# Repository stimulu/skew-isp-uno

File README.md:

# Skew ISP Uno

[Order the PCB on OSH Park](https://oshpark.com/shared_projects/m8nYVVg6)

### Features
Skew ISP Uno is an ISP programming shield for Arduino Uno.  
Use it with the sketch described at [Arduino.cc's Arduino ISP Tutorial](https://www.arduino.cc/en/Tutorial/ArduinoISP#toc5).   
This shield enables programming of AVR chips notably ATTiny or ATMega.  
One special feature is the presence of a 6 positions Molex PicoBlade connector.

This board features slots for:

* ATTiny ×4
* ATTiny ×5
* a 2×3 pins ISP port
* a 6 pins Molex PicoBlade

### BOM

##### Required 

* 1 × capacitor 10µF ([Digikey 1572-1289-ND](https://www.digikey.com/products/en?keywords=1572-1289-ND))
* 4 + 7 positions connector header 2.54mm pitch ([Digikey 609-5133-ND](https://www.digikey.com/products/en?keywords=609-5133-ND))

##### Optional 
* 1 × connector header 6 positions 2.54mm pitch ([Digikey 609-3234-ND](https://www.digikey.com/products/en?keywords=609-3234-ND))
* 1 × IC socket 8 positions 2.54mm pitch ([Digikey 2057-ICS-308-T-ND](https://www.digikey.com/products/en?keywords=2057-ICS-308-T-ND))
* 1 × IC socket 14 positions 2.54mm pitch ([Digikey AE9989-ND](https://www.digikey.com/products/en?keywords=AE9989-ND))
* 1 × Molex PicoBlade connector header 6 positions ([Digikey WM1735-ND](https://www.digikey.com/products/en?keywords=WM1735-ND))
* 1 × Molex PicoBlade cable assembly 6 positions ([Digikey WM15267-ND](https://www.digikey.com/products/en?keywords=WM15267-ND))
* 2 × 200 ohm 0805 SMD resistor ([Digikey 311-200CRCT-ND](https://www.digikey.com/products/en?keywords=311-200CRCT-ND))
* 2 × red LED 0603 ([Digikey 732-4978-1-ND](https://www.digikey.com/products/en?keywords=732-4978-1-ND))

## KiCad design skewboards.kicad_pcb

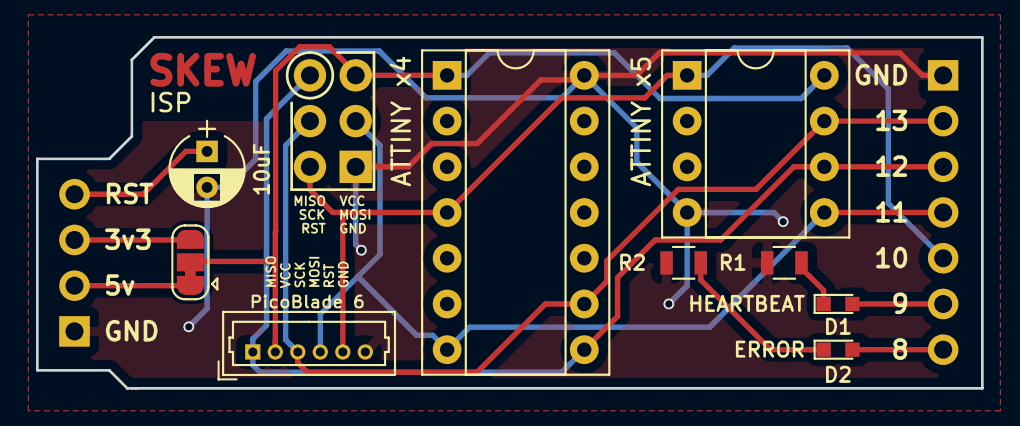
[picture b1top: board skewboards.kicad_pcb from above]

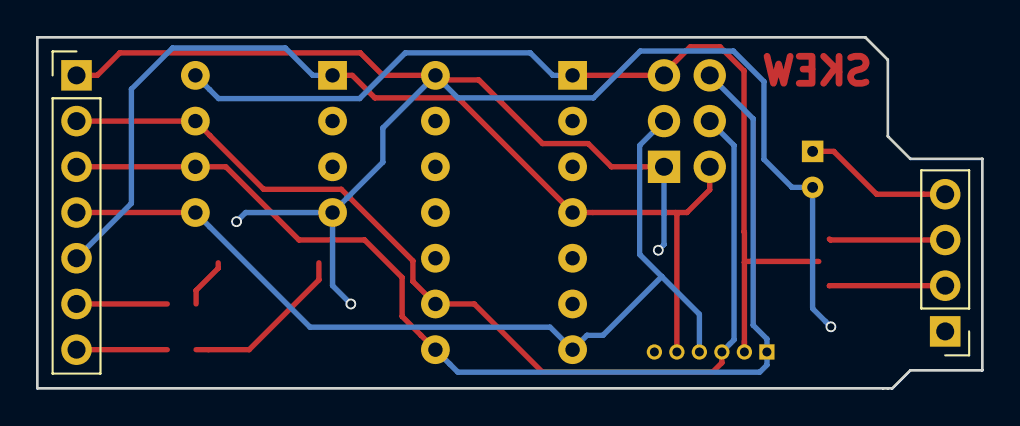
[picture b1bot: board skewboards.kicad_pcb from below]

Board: 2 copper layers, 52.5 x 19.5 mm, 12 parts (2 on the bottom side), 13 nets.

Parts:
C1: 10uF; CP_Radial_D4.0mm_P2.00mm
D1: HEARTBEAT; LED_0603
D2: ERROR; LED_0603
J1: UNO POWER; Pin_Header_Straight_1x04_Pitch2.54mm
J2: UNO PIN 8-13, GND; Pin_Header_Straight_1x07_Pitch2.54mm
J4: ICSP_header; ICSP_th
J5: microblade 6; Molex_PicoBlade_53047-0610_06x1.25mm_Straight
JP1: Jumper_3_Bridged12; SolderJumper-3_P1.3mm_Bridged12_RoundedPad1.0x1.5mm
R1, R2: R; R_0805
S8: ATTINY x5; DIP-8_W7.62mm_Socket
S14: ATTINY x4; DIP-14_W7.62mm_Socket

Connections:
/ERROR: D2.2, J2.7
/HEARTBEAT: D1.2, J2.6
/MISO: J2.3, J4.1, J5.1, S8.6, S14.8
/MOSI: J2.4, J4.4, J5.4, S8.5, S14.7
/RESET: J2.5, J4.5, J5.5, S8.1, S14.4
/RST: C1.1, J1.4
/SCK: J2.2, J4.3, J5.3, S8.7, S14.9
GND: C1.2, J1.1, J2.1, J4.6, J5.6, R1.2, R2.2, S8.4, S14.14
unnamed: D1.1, R1.1
unnamed: D2.1, R2.1
unnamed: J1.2, JP1.1
unnamed: J1.3, JP1.3
VCC: J4.2, J5.2, JP1.2, S8.8, S14.1

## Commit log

2019-02-27 Init with existing files
2019-02-27 Add image to readme
2019-02-27 Add OSH Park project link
2019-03-01 Add interactiv BOM
2019-03-01 Add Gerbers
